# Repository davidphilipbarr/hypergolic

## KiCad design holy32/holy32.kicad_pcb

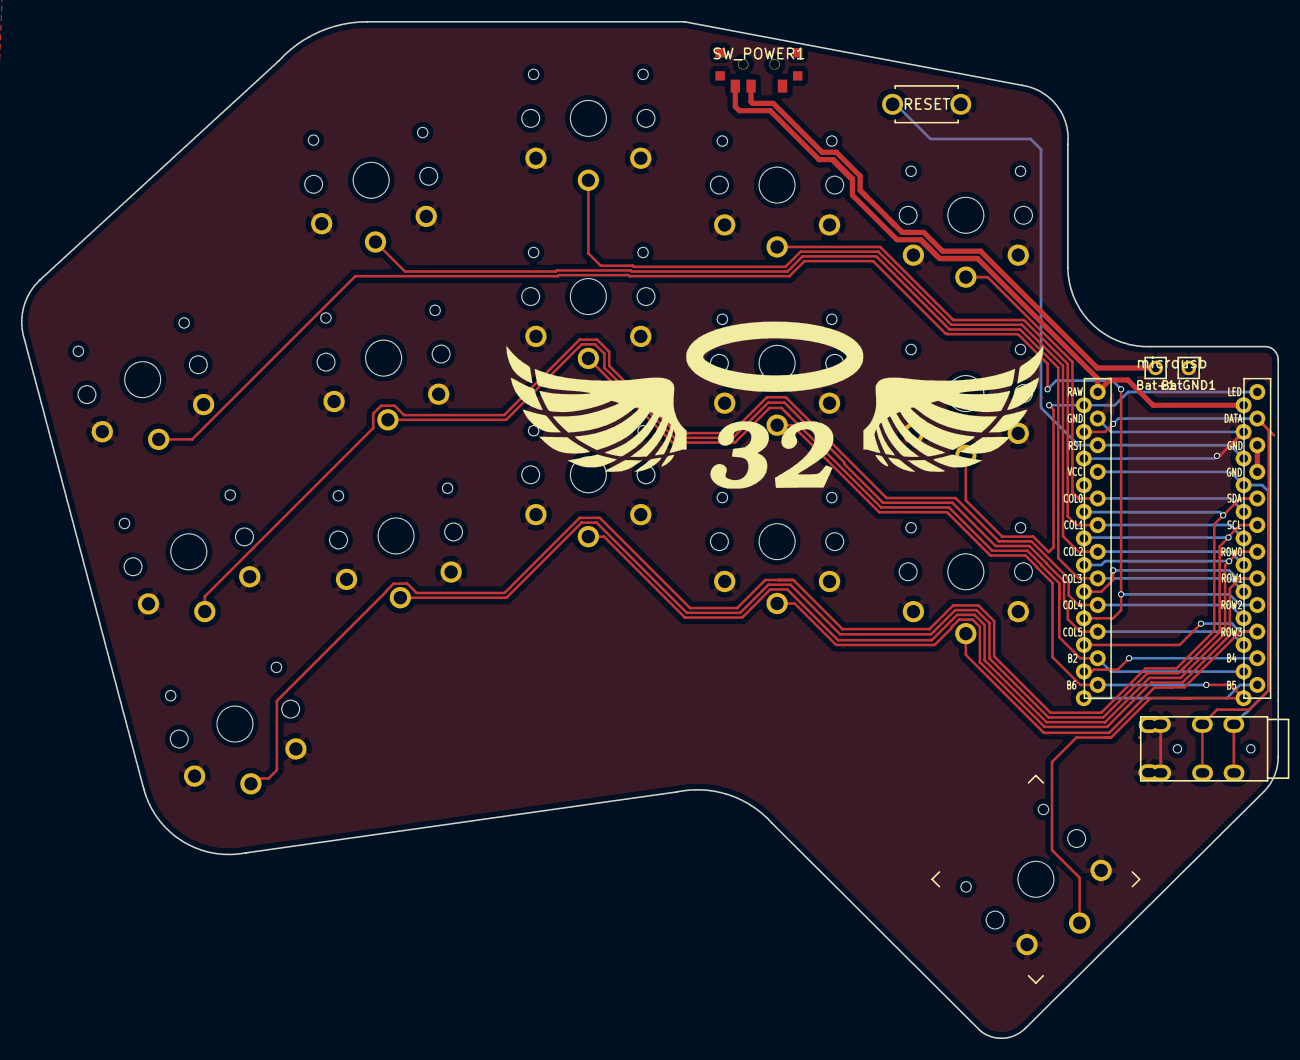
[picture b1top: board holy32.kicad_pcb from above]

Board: 2 copper layers, 119.8 x 96.9 mm, 22 parts (0 on the bottom side), 21 nets.

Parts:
Bat+1: MountingHole_Pad; 1pin_conn
BatGND1: MountingHole_Pad; 1pin_conn
Jack0: TRRS; TRRS-PJ-DPB2
RSW1: SW_Push; ResetSW
SW2, SW3, SW4, SW5, SW6, SW8, SW9, SW10, SW11, SW12, SW14, SW15, SW16, SW17, SW18: SW_Push; SW_PG1350_rev_DPB
SW20: SW_Push; SW_PG1350_15_reversible_b2
SW_POWER1: SW_SPDT; SPDT_C128955
U1: ProMicro-kbd; ProMicro_v2

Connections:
BT+: Bat+1.1, SW_POWER1.2
Switch1: SW2.1, U1.9
Switch2: SW3.1, U1.17
Switch3: SW4.1, U1.18
Switch4: SW5.1, U1.19
Switch5: SW6.1, U1.20
Switch6: SW8.1, U1.16
Switch7: SW9.1, U1.15
Switch8: SW10.1, U1.14
Switch9: SW11.1, SW20.1, U1.13
Switch10: SW12.1, U1.1
Switch11: SW14.1, U1.5
Switch12: SW15.1, U1.6
Switch13: SW16.1, U1.7
Switch14: SW17.1, U1.8
Switch15: SW18.1, U1.10
Switch18: Jack0.R1, U1.2
gnd: BatGND1.1, Jack0.S, Jack0.T, RSW1.1, SW2.2, SW3.2, SW4.2, SW5.2, SW6.2, SW8.2, SW9.2, SW10.2, SW11.2, SW12.2, SW14.2, SW15.2, SW16.2, SW17.2, SW18.2, SW20.2, U1.3, U1.4, U1.23
raw: SW_POWER1.3, U1.24
reset: RSW1.2, U1.22
vcc: Jack0.R2, U1.21
